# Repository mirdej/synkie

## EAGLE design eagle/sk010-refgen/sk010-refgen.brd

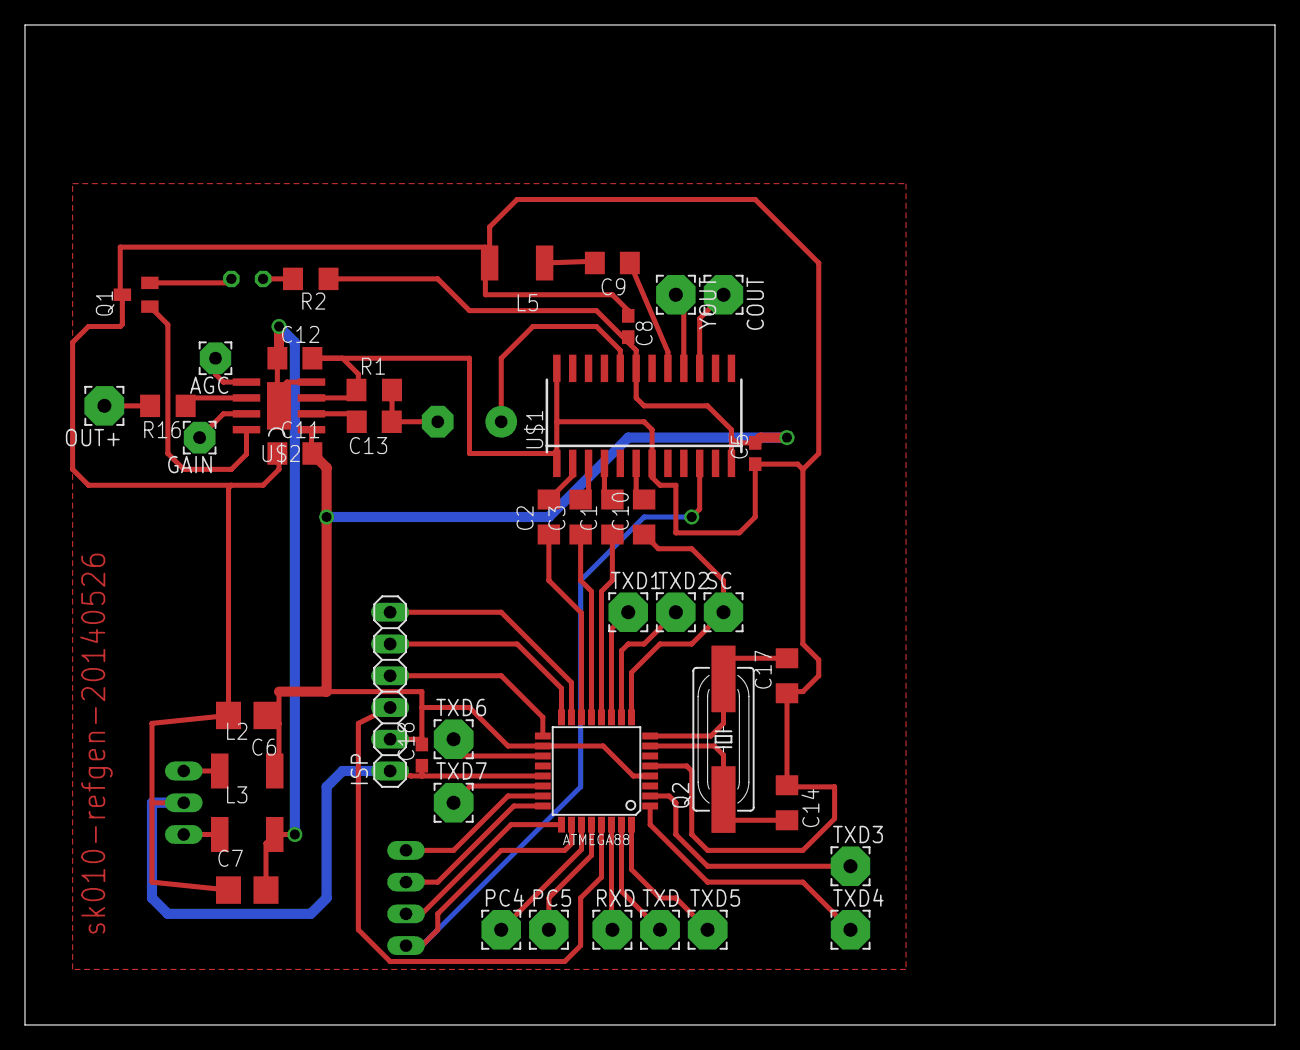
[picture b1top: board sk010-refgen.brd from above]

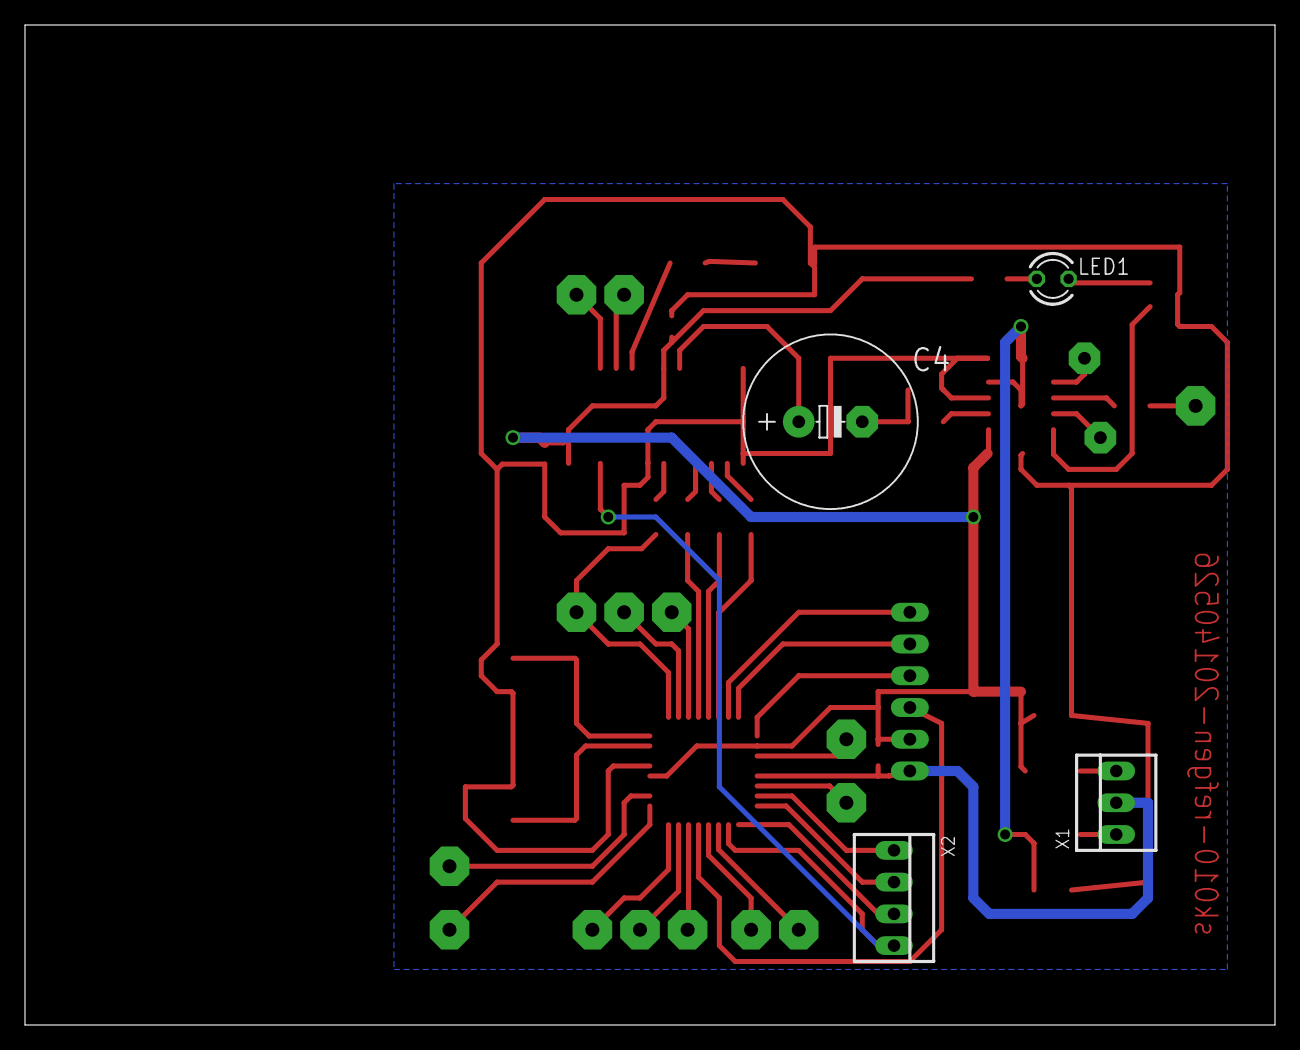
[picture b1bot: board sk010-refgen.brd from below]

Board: 2 copper layers, 100.0 x 80.0 mm, 48 parts (4 on the bottom side), 48 nets.

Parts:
AGC: 2,54/1,0
ATMEGA88: ATMEGA88; TQFP32-08
C1, C2, C3, C9, C10, C11, C12: C1206
C4: E5-13
C5, C8, C18: C0603
C6, C7: 10u; CT3528
C13: 1u; C1206
C14, C17: 15p; C1206
COUT: 3,17/1,1
GAIN: 2,54/1,0
ISP: 1X06
L2, L3, L5: L5038P
LED1: LED3MM
OUT+: 3,17/1,1
PC4, PC5: 3,17/1,1
Q1: BC857ASMD; SOT23-BEC
Q2: 17.734475MHz; HC49UP
R1, R16: 75; R1206
R2: 300; R1206
RXD: 3,17/1,1
SC: 3,17/1,1
TXD, TXD1, TXD2, TXD3, TXD4, TXD5, TXD6, TXD7: 3,17/1,1
U$1: BH7236-RGB; SO24N
U$2: MAX7450; SO08-EXP
X1: 22-23-2031
X2: 22-23-2041
YOUT: 3,17/1,1

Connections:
+5V: ATMEGA88.4, ATMEGA88.18, C5.2, C6.+, C8.2, C11.2, C18.2, ISP.2, L2.2, R2.1, U$1.12, U$1.19, U$2.1
-5V: C7.-, C12.1, L3.2, U$2.4, U$2.EXP
GND: ATMEGA88.5, ATMEGA88.21, C5.1, C6.-, C7.+, C8.1, C11.1, C12.2, C14.1, C17.1, C18.1, ISP.1, L5.2, Q1.C, R1.1, U$1.1, U$1.7, U$1.24, U$2.3, X1.2
MISO: ATMEGA88.16, ISP.5
MOSI: ATMEGA88.15, ISP.6
unnamed: C1.2, U$1.4
unnamed: ATMEGA88.9, C10.1, SC.1
unnamed: C2.2, U$1.2
unnamed: C3.2, U$1.3
unnamed: C9.1, U$1.17
unnamed: C9.2, L5.1
unnamed: ATMEGA88.23, X2.1
unnamed: ATMEGA88.12, C1.1
unnamed: ATMEGA88.25, X2.3
unnamed: ATMEGA88.13, C3.1
unnamed: L2.1, X1.3
unnamed: C10.2, U$1.6
unnamed: AGC.1, U$2.5
unnamed: Q1.B, U$2.8
unnamed: L3.1, X1.1
unnamed: LED1.A, R2.2
unnamed: ATMEGA88.29, ISP.3
unnamed: LED1.K, Q1.E
unnamed: C13.2, U$2.2
unnamed: ATMEGA88.14, C2.1
unnamed: ATMEGA88.26, U$1.10, X2.4
unnamed: GAIN.1, U$2.7
unnamed: C4.-, C13.1, R1.2
unnamed: ATMEGA88.28, PC5.1
unnamed: U$1.16, YOUT.1
unnamed: ATMEGA88.27, PC4.1
unnamed: ATMEGA88.24, X2.2
unnamed: ATMEGA88.22, TXD7.1
unnamed: COUT.1, U$1.15
unnamed: ATMEGA88.30, RXD.1
unnamed: R16.1, U$2.6
unnamed: OUT+.1, R16.2
unnamed: ATMEGA88.7, C14.2, Q2.1
unnamed: ATMEGA88.19, TXD6.1
unnamed: ATMEGA88.31, TXD.1
unnamed: ATMEGA88.32, TXD5.1
unnamed: ATMEGA88.1, TXD4.1
unnamed: ATMEGA88.8, C17.2, Q2.2
unnamed: ATMEGA88.2, TXD3.1
unnamed: ATMEGA88.10, TXD2.1
unnamed: ATMEGA88.11, TXD1.1
unnamed: C4.+, U$1.20
SCK: ATMEGA88.17, ISP.4

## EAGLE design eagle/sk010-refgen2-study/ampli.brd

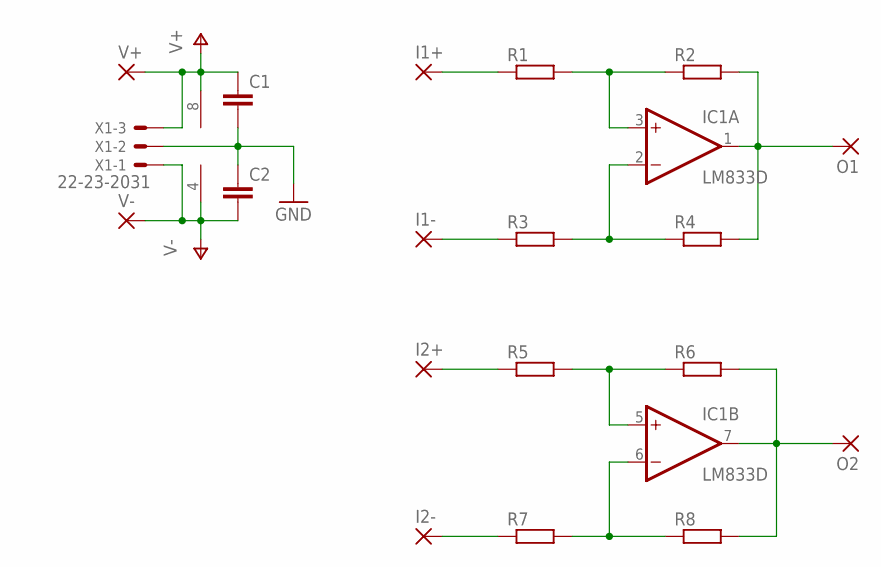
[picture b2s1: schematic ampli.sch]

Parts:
C1, C2: C-EUC0805; C0805
I1+, I1-, I2+, I2-: 3,17/1,1
IC1: LM833D; SO08
O1, O2: 3,17/1,1
R1, R2, R3, R4, R5, R6, R7, R8: R-EU_R1206; R1206
V+: 3,17/1,1
V-: 3,17/1,1
X1: 22-23-2031

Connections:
GND: C1.2, C2.1, X1.2
unnamed: IC1.3 (+IN), R1.2, R2.1
unnamed: IC1.1 (OUT), O1.1, R2.2, R4.2
unnamed: IC1.2 (-IN), R3.2, R4.1
unnamed: I1+.1, R1.1
unnamed: I1-.1, R3.1
unnamed: I2+.1, R5.1
unnamed: IC1.5 (+IN), R5.2, R6.1
unnamed: IC1.7 (OUT), O2.1, R6.2, R8.2
unnamed: IC1.6 (-IN), R7.2, R8.1
unnamed: I2-.1, R7.1
V+: C1.1, IC1.8 (V+), V+.1, X1.3
V-: C2.2, IC1.4 (V-), V-.1, X1.1

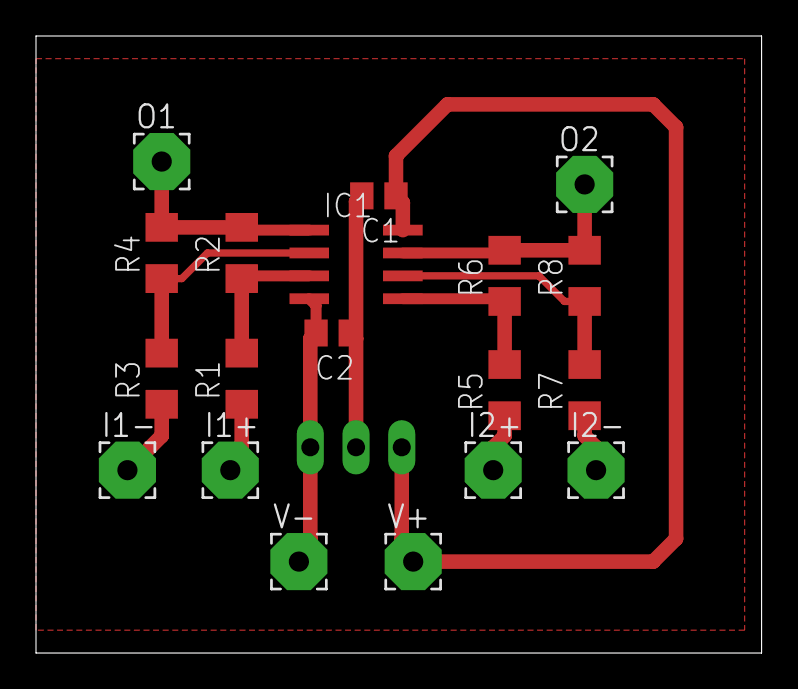
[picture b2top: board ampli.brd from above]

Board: 2 copper layers, 40.3 x 34.3 mm, 20 parts (1 on the bottom side), 13 nets.

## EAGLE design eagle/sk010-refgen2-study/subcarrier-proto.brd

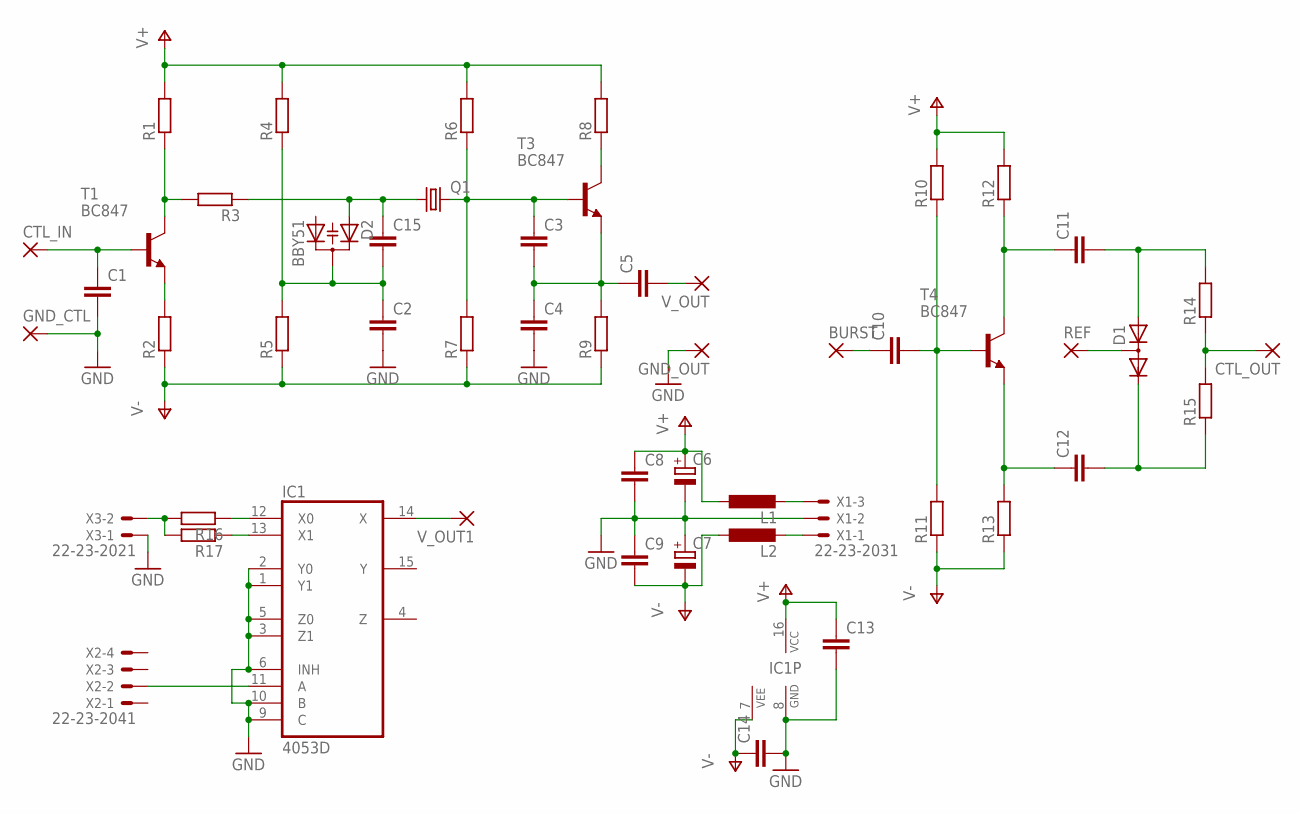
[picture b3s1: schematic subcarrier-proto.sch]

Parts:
BURST: WIREPAD3,17/1,1; 3,17/1,1
C1, C2, C3, C4, C5, C10, C11, C12, C15: C-EUC1210; C1210
C6, C7: CPOL-EUCT3528; CT3528
C8, C9, C13, C14: C-EUC0805; C0805
CTL_IN: WIREPAD3,17/1,1; 3,17/1,1
CTL_OUT: 3,17/1,1
D1: DIODE_2CACA-SOT23; SOT23
D2: BBY51; SOT23
GND_CTL: WIREPAD3,17/1,1; 3,17/1,1
GND_OUT: 3,17/1,1
IC1: 4053D; SO16
L1, L2: L-EUL5038P; L5038P
Q1: CRYSTALHC49UP; HC49UP
R1, R2, R3, R4, R5, R6, R7, R8, R9, R10, R11, R12, R13, R14, R15, R16, R17: R-EU_R1210; R1210
REF: 3,17/1,1
T1, T3, T4: BC847; SOT23
V_OUT, V_OUT1: 3,17/1,1
X1: 22-23-2031
X2: 22-23-2041
X3: 22-23-2021

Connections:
GND: C1.2, C2.2, C4.2, C6.-, C7.+, C8.2, C9.1, C13.2, C14.2, GND_CTL.1, GND_OUT.1, IC1.1 (Y1), IC1.2 (Y0), IC1.3 (Z1), IC1.5 (Z0), IC1.6 (INH), IC1.8 (GND), IC1.9 (C), IC1.10 (B), X1.2, X3.1
unnamed: C1.1, CTL_IN.1, T1.1 (B)
unnamed: C5.2, V_OUT.1
unnamed: R1.1, R3.2, T1.3 (C)
unnamed: R2.2, T1.2 (E)
unnamed: C2.1, C15.2, D2.3 (C), R4.1, R5.2
unnamed: C15.1, D2.1 (A1), Q1.1, R3.1
unnamed: L1.2, X1.3
unnamed: L2.2, X1.1
unnamed: C3.1, Q1.2, R6.1, R7.2, T3.1 (B)
unnamed: R8.1, T3.3 (C)
unnamed: C3.2, C4.1, C5.1, R9.2, T3.2 (E)
unnamed: BURST.1, C10.1
unnamed: C10.2, R10.1, R11.2, T4.1 (B)
unnamed: C12.1, R13.2, T4.2 (E)
unnamed: C11.1, R12.1, T4.3 (C)
unnamed: C11.2, D1.1 (A), R14.2
unnamed: C12.2, D1.2 (C), R15.1
unnamed: CTL_OUT.1, R14.1, R15.2
unnamed: IC1.12 (X0), R16.1
unnamed: IC1.13 (X1), R17.1
unnamed: D1.3 (AC), REF.1
unnamed: R16.2, R17.2, X3.2
unnamed: IC1.11 (A), X2.2
unnamed: IC1.14 (X), V_OUT1.1
V+: C6.+, C8.1, C13.1, IC1.16 (VCC), L1.1, R1.2, R4.2, R6.2, R8.2, R10.2, R12.2
V-: C7.-, C9.2, C14.1, IC1.7 (VEE), L2.1, R2.1, R5.1, R7.1, R9.1, R11.1, R13.1

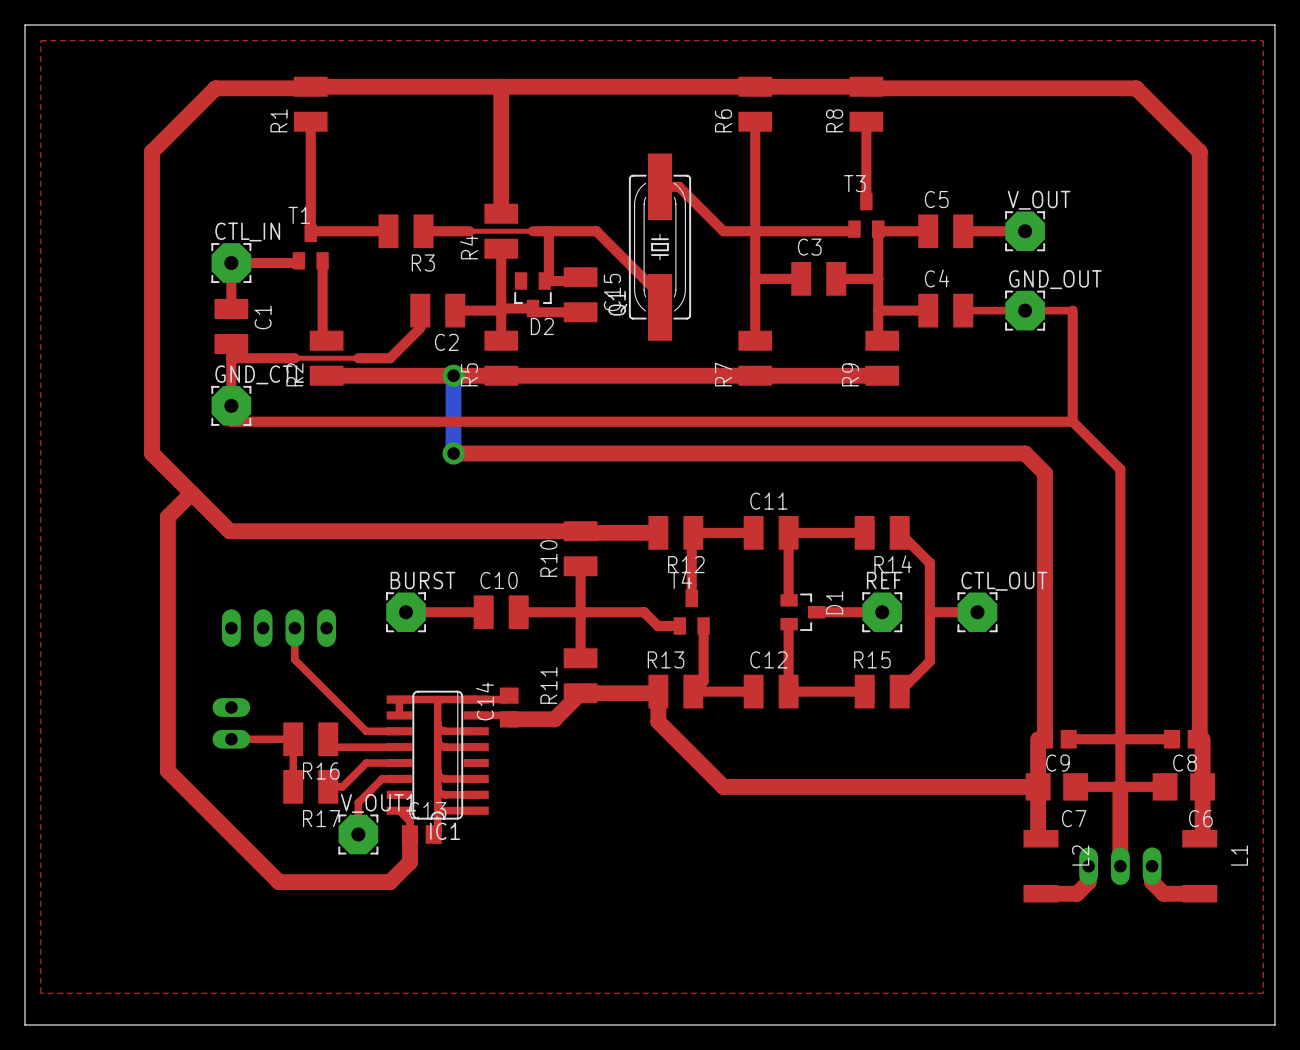
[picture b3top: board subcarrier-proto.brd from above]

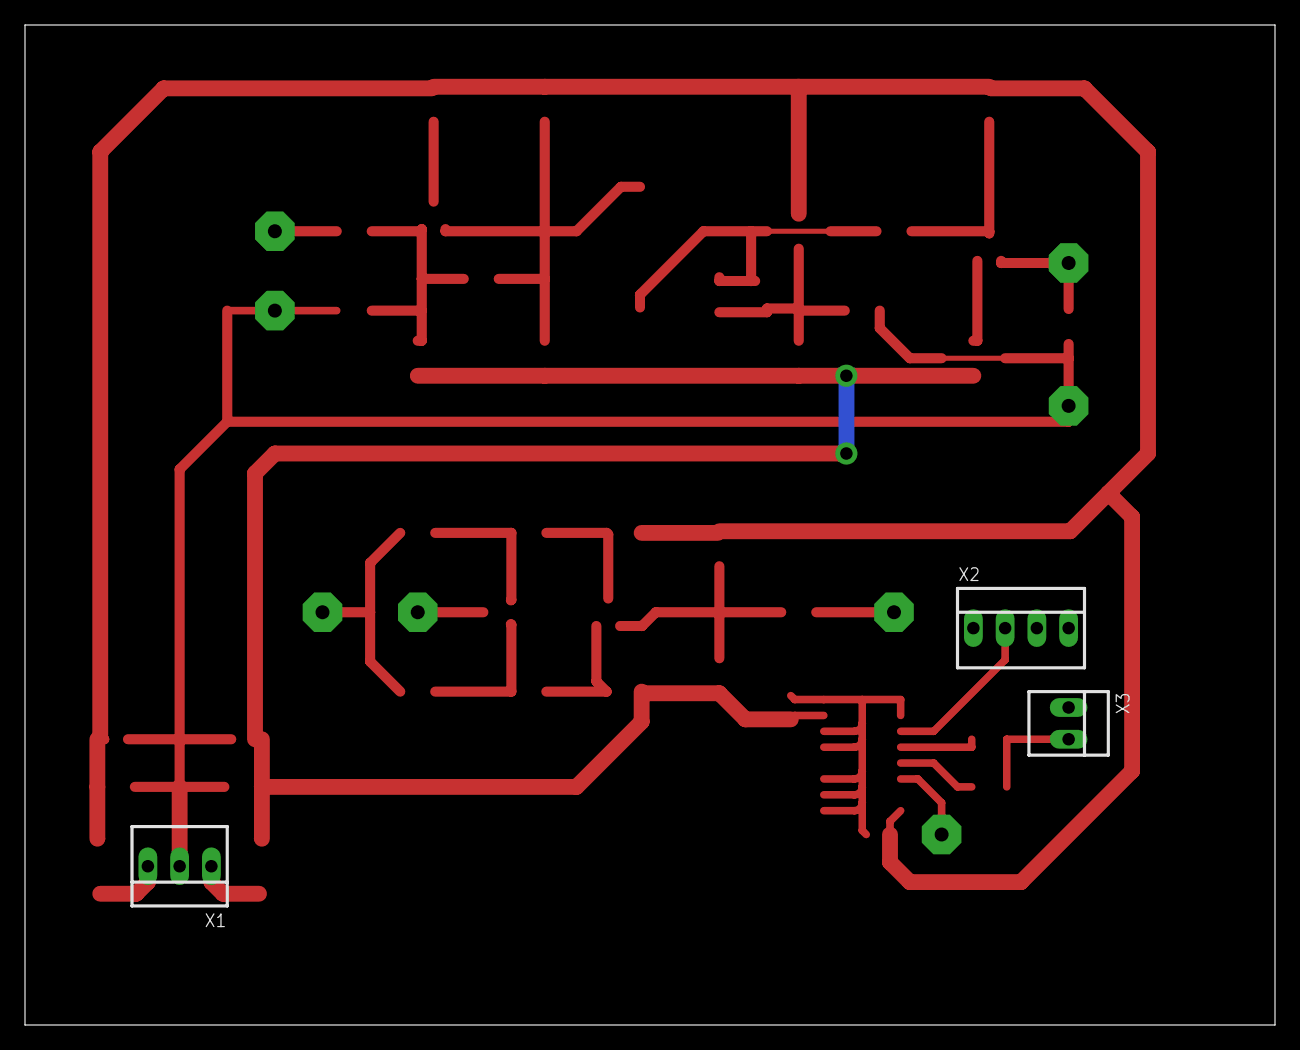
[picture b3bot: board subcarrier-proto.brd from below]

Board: 2 copper layers, 100.0 x 80.0 mm, 52 parts (3 on the bottom side), 27 nets.

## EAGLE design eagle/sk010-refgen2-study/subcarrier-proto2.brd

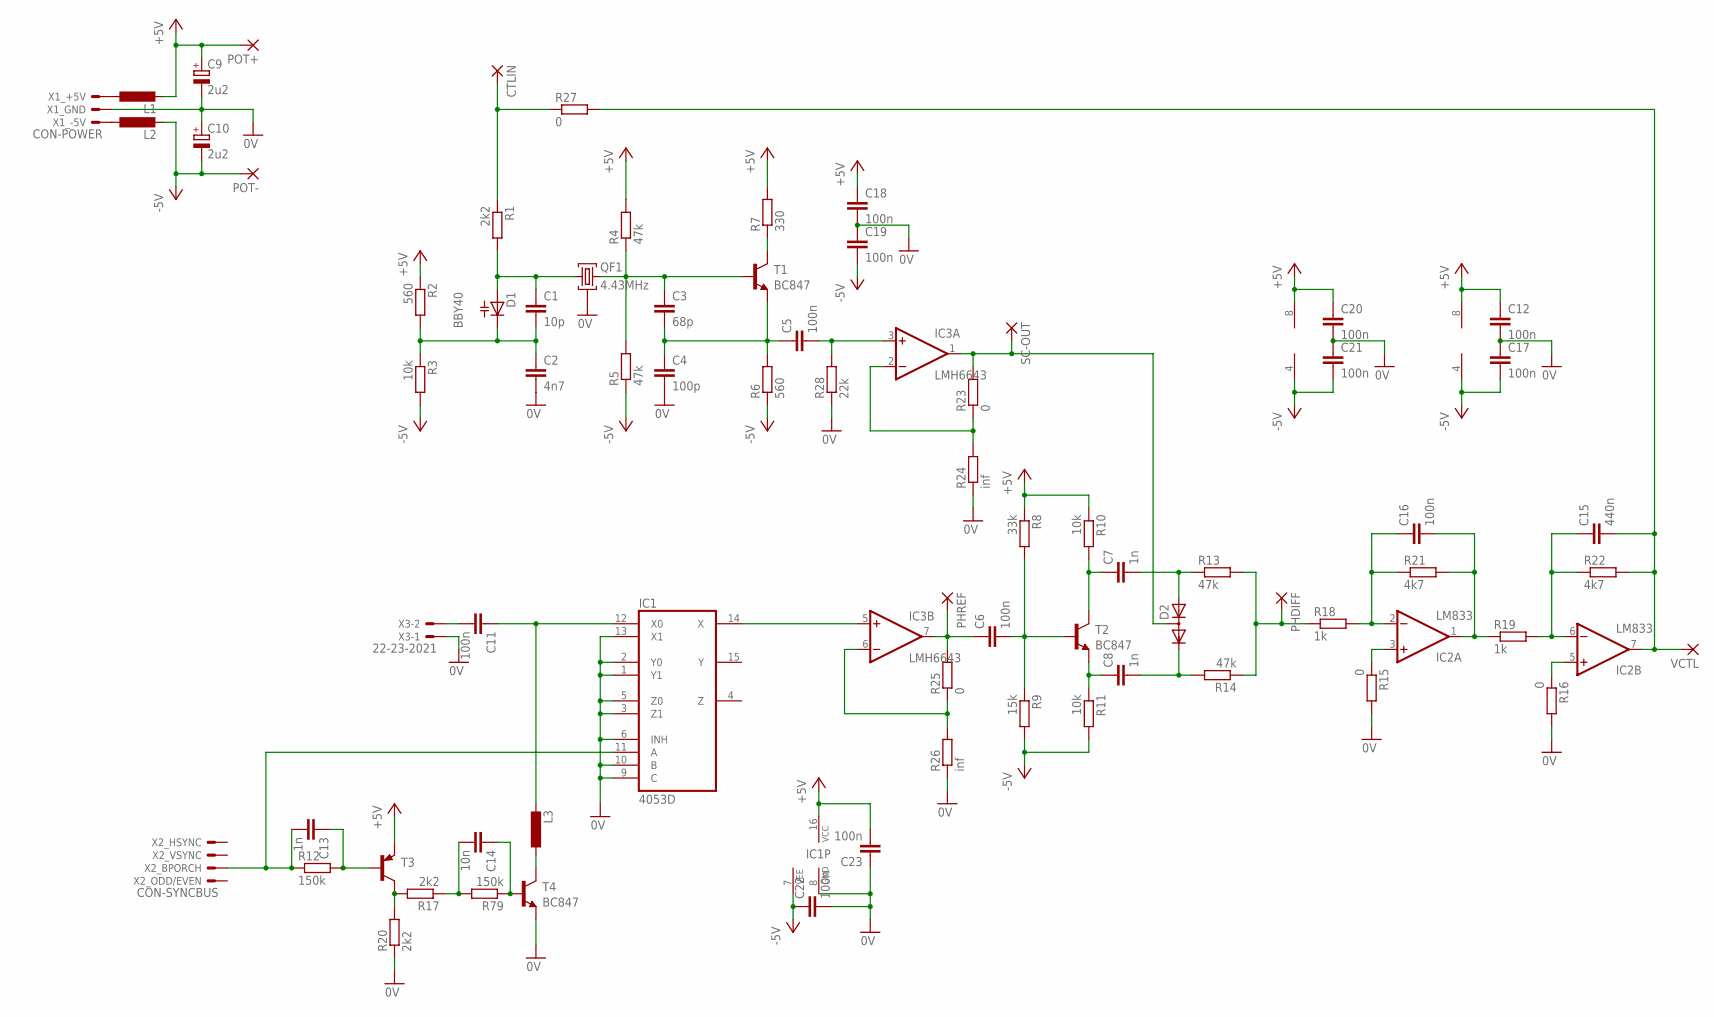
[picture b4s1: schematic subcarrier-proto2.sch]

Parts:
C1: 10p; C1206
C2: 4n7; C1206
C3: 68p; C1206
C4: 100p; C1206
C5, C6, C11, C12, C16, C17, C18, C19, C20, C21, C22, C23: 100n; C1206
C7, C8, C13: 1n; C1206
C9, C10: 2u2; CT3528
C14: 10n; C1206
C15: 440n; C1206
CTLIN: 3,17/1,1
D1: BBY40; SOT23
D2: DIODE_2CACA-SOT23; SOT23
IC1: 4053D; SO16
IC2: LM833; SO08
IC3: LMH6643; SO08
L1, L2, L3: L-EUL5038P; L5038P
PHDIFF: 3,17/1,1
PHREF: 3,17/1,1
POT+: 3,17/1,1
POT-: 3,17/1,1
QF1: 4.43MHz; SMD-CRYSTAL-GND
R1, R17, R20: 2k2; R1206
R2, R6: 560; R1206
R3, R10, R11: 10k; R1206
R4, R5, R13, R14: 47k; R1206
R7: 330; R1206
R8: 33k; R1206
R9: 15k; R1206
R12, R79: 150k; R1206
R15, R16, R23, R25, R27: 0; R1206
R18, R19: 1k; R1206
R21, R22: 4k7; R1206
R24, R26: inf; R1206
R28: 22k; R1206
SC-OUT: 3,17/1,1
T1, T2, T4: BC847; SOT23-BEC
T3: TRANS-PNPSOT23-BEC; SOT23-BEC
VCTL: 3,17/1,1
X1: CON-POWER; 22-23-2031
X2: CON-SYNCBUS; 22-23-2041
X3: 22-23-2021

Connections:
0V: C2.2, C4.2, C9.-, C10.+, C12.2, C17.1, C18.2, C19.1, C20.2, C21.1, C22.2, C23.1, IC1.1 (Y1), IC1.2 (Y0), IC1.3 (Z1), IC1.5 (Z0), IC1.6 (INH), IC1.8 (GND), IC1.9 (C), IC1.10 (B), IC1.13 (X1), QF1.P$3 (2), R15.2, R16.2, R20.1, R24.1, R26.1, R28.1, T4.E, X1.2, X3.1
+5V: C9.+, C12.1, C18.1, C20.1, C23.2, IC1.16 (VCC), IC2.8 (V+), IC3.8 (V+), L1.2, POT+.1, R2.1, R4.2, R7.2, R8.1, R10.1, T3.E
-5V: C10.-, C17.2, C19.2, C21.2, C22.1, IC1.7 (VEE), IC2.4 (V-), IC3.4 (V-), L2.2, POT-.1, R3.2, R5.1, R6.1, R9.2, R11.2
unnamed: C13.1, R12.2, T3.B
unnamed: C13.2, IC1.11 (A), R12.1, X2.2
unnamed: C1.1, D1.1 (A1), QF1.P$1 (1), R1.2
unnamed: C3.1, QF1.P$2 (3), R4.1, R5.2, T1.B
unnamed: C1.2, C2.1, D1.3 (C), R2.2, R3.1
unnamed: C3.2, C4.1, C5.1, R6.2, T1.E
unnamed: C5.2, IC3.3 (+IN), R28.2
unnamed: R7.1, T1.C
unnamed: C6.2, R8.2, R9.1, T2.B
unnamed: C8.1, R11.1, T2.E
unnamed: C7.1, R10.2, T2.C
unnamed: PHDIFF.1, R13.2, R14.1, R18.1
unnamed: C7.2, D2.1 (A), R13.1
unnamed: C8.2, D2.2 (C), R14.2
unnamed: C6.1, IC3.7 (OUT), PHREF.1, R25.2
unnamed: C11.2, X3.2
unnamed: C11.1, IC1.12 (X0), L3.2
unnamed: C16.1, IC2.2 (-IN), R18.2, R21.1
unnamed: IC2.3 (+IN), R15.1
unnamed: IC2.5 (+IN), R16.1
unnamed: C16.2, IC2.1 (OUT), R19.1, R21.2
unnamed: C15.1, IC2.6 (-IN), R19.2, R22.1
unnamed: C15.2, IC2.7 (OUT), R22.2, R27.2, VCTL.1
unnamed: L1.1, X1.3
unnamed: L2.1, X1.1
unnamed: CTLIN.1, R1.1, R27.1
unnamed: D2.3 (AC), IC3.1 (OUT), R23.2, SC-OUT.1
unnamed: IC3.2 (-IN), R23.1, R24.2
unnamed: IC3.6 (-IN), R25.1, R26.2
unnamed: IC1.14 (X), IC3.5 (+IN)
unnamed: L3.1, T4.C
unnamed: C14.1, R79.1, T4.B
unnamed: R17.2, R20.2, T3.C
unnamed: C14.2, R17.1, R79.2

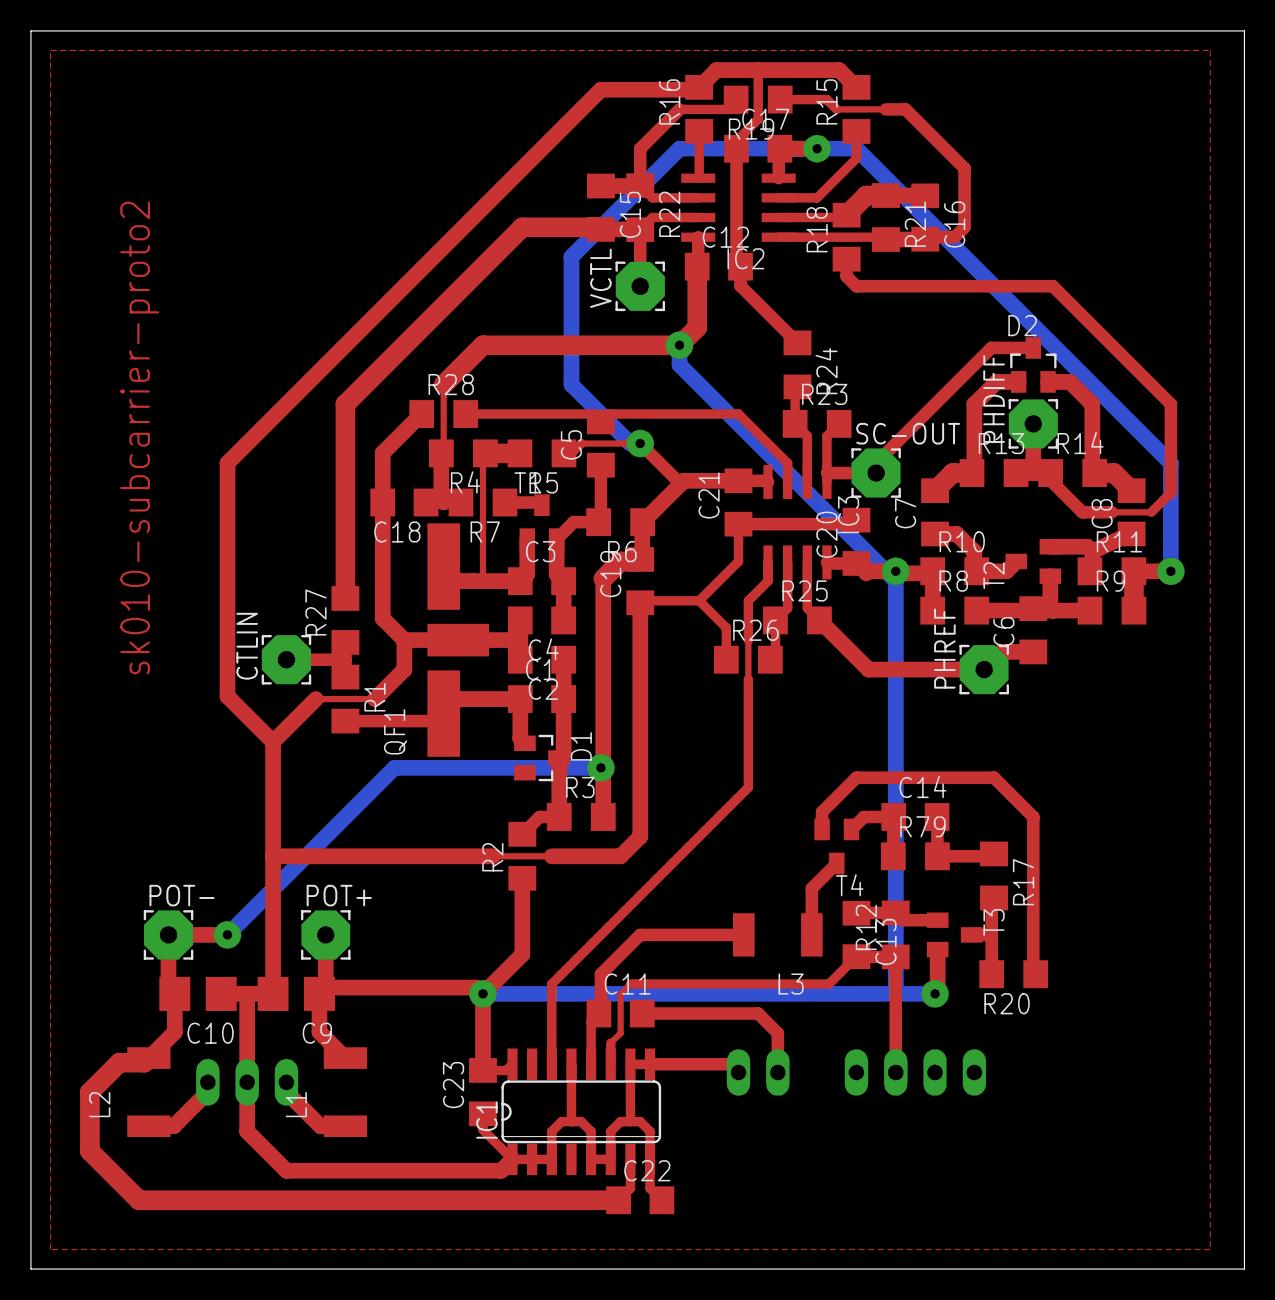
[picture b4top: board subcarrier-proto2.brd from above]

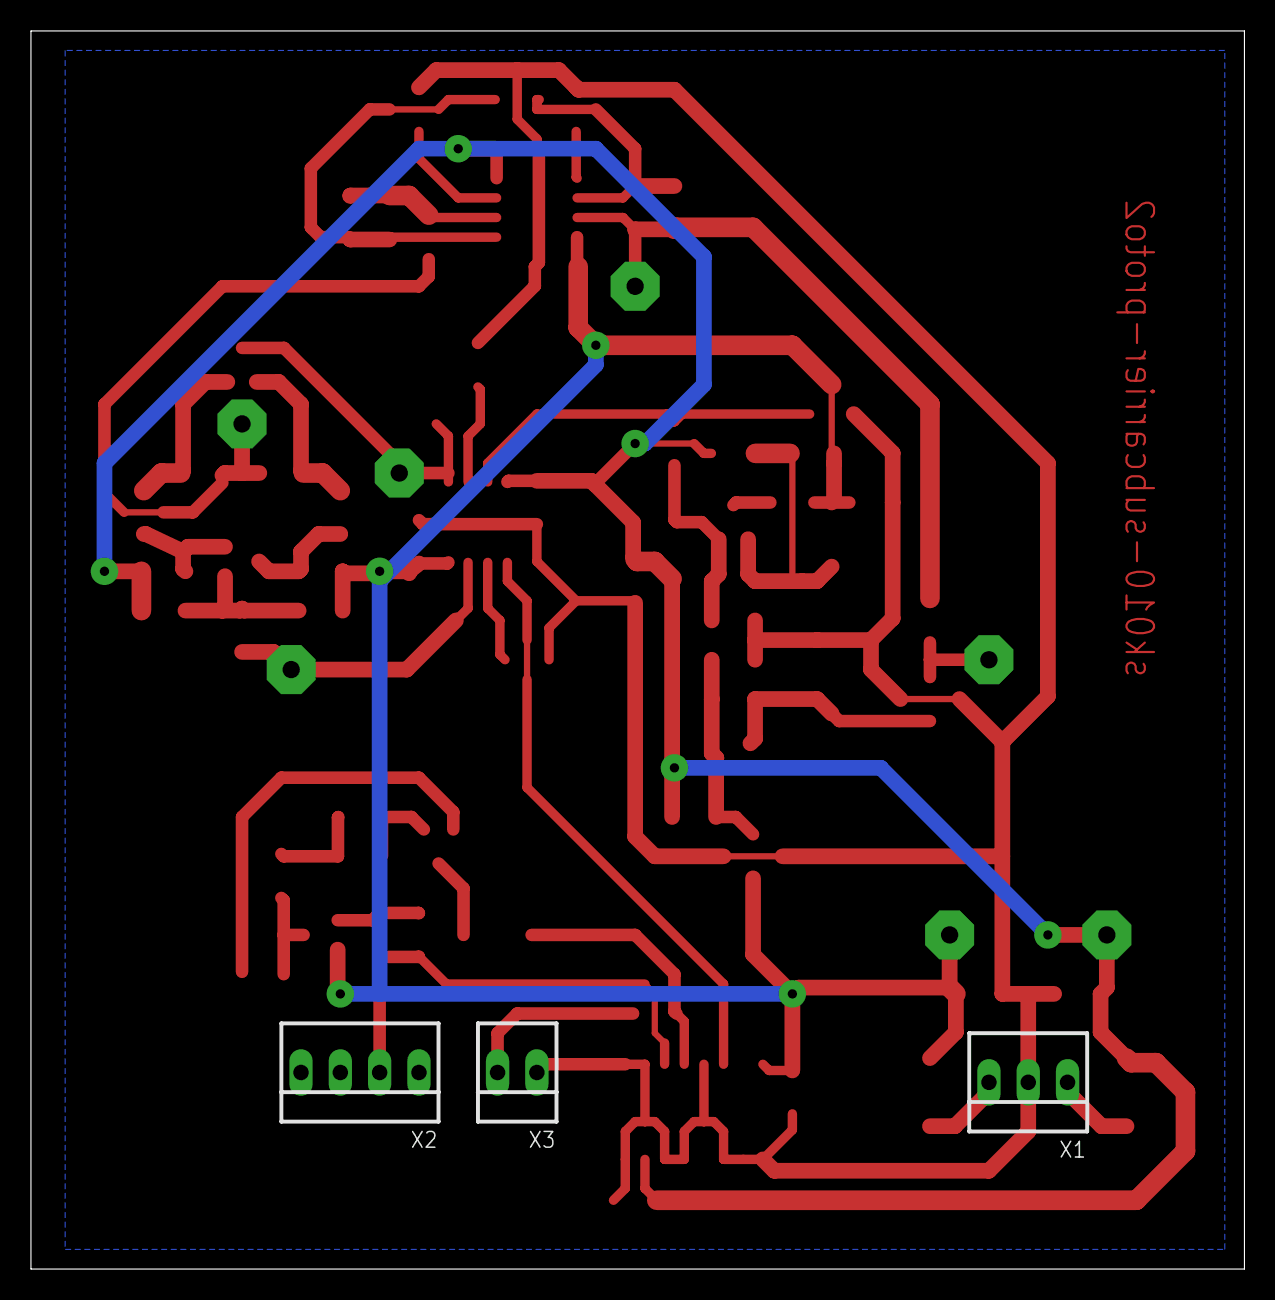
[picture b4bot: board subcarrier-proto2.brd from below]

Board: 2 copper layers, 78.4 x 80.0 mm, 75 parts (3 on the bottom side), 37 nets.

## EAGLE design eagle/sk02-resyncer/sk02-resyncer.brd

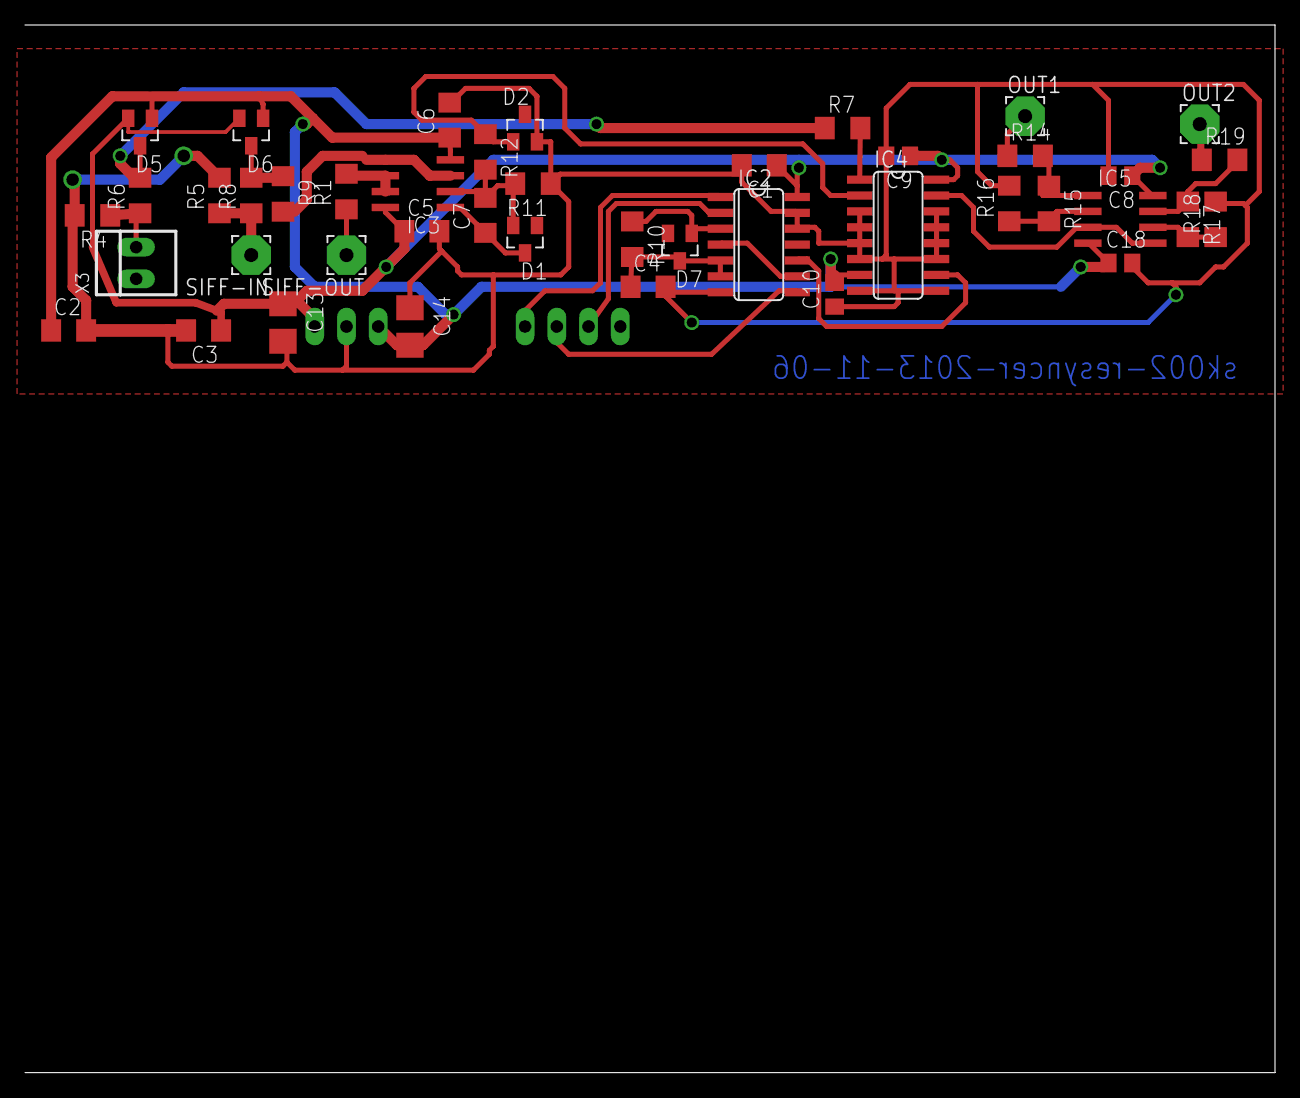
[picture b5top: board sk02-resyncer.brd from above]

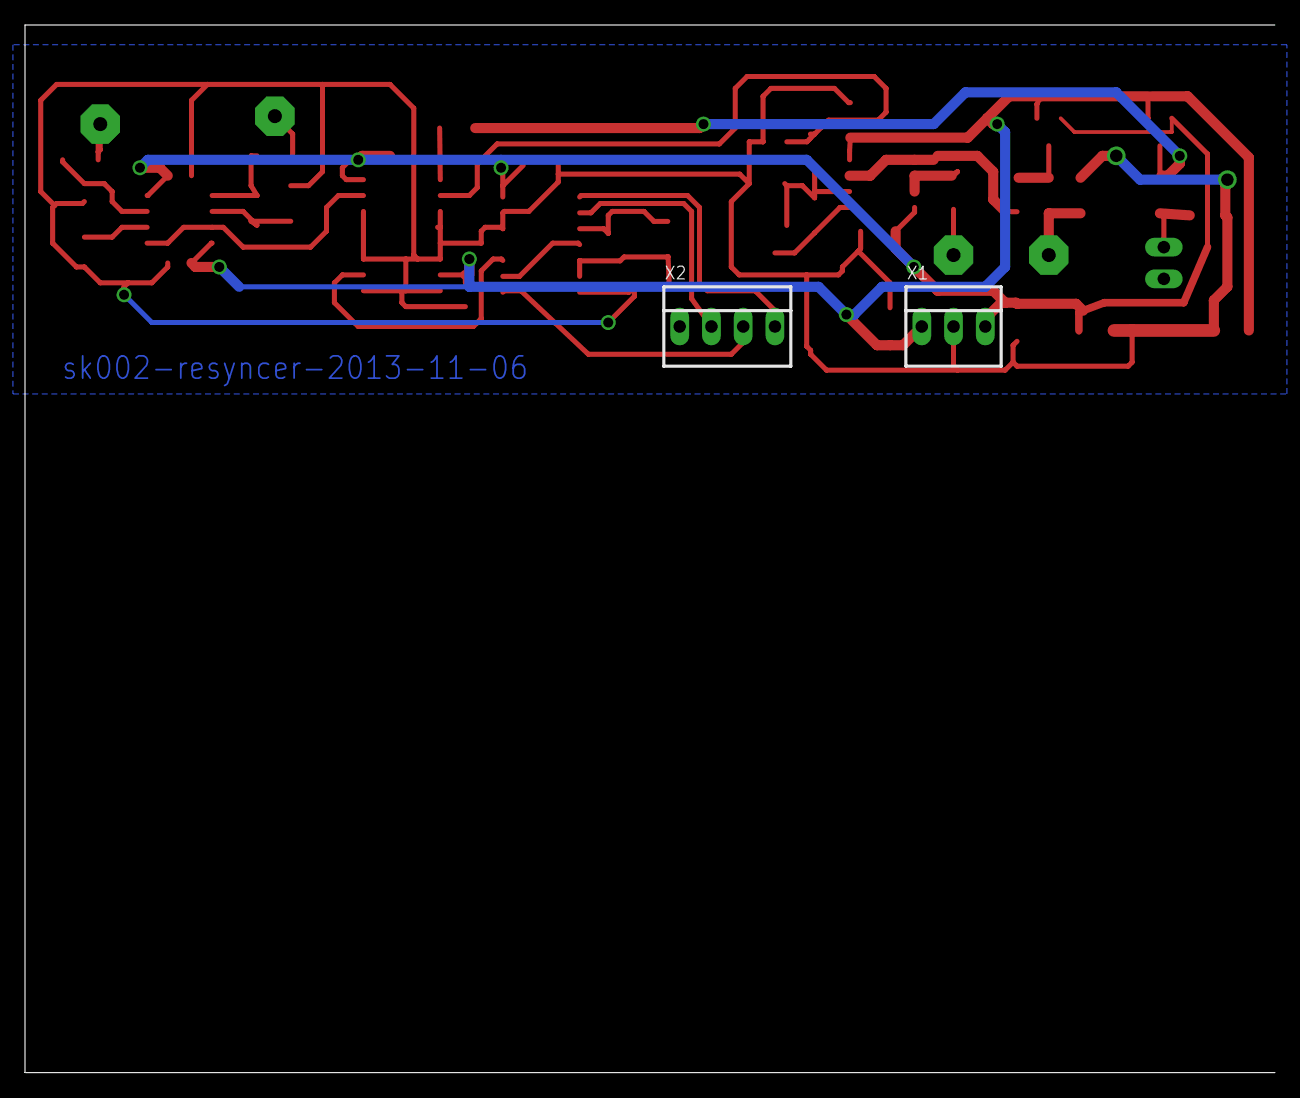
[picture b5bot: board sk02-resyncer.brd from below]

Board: 2 copper layers, 100.0 x 83.8 mm, 45 parts (2 on the bottom side), 28 nets.

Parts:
C1, C2, C3, C5, C6: 100n; C1206
C4: 120p; C1206
C7: 10p; C1206
C8, C9, C10, C18: 100n; C0805
C13, C14: 2u2tantal; CT3528
D1, D5, D6: BAT54S-L44; SOT23
D2: 1PS302; SOT23
D7: BAS70-04; SOT23
IC2: 4011D; SO14
IC3, IC5: LM833D; SO08
IC4: 4053D; SO16
OUT1, OUT2: 3,17/1,1
R1, R14, R19: 75; R1206
R4, R5: 47k; R1206
R6, R7, R8, R9: 100; R1206
R10: 2k2; R1206
R11, R12: 1k; R1206
R15, R16, R17, R18: 200; R1206
SIFF-IN: 3,17/1,1
SIFF-OUT: 3,17/1,1
X1: 22-23-2031
X2: 22-23-2041
X3: 22-23-2021

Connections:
+5V: C1.1, C3.1, C5.1, C8.1, C9.1, C13.+, D5.2, D6.2, IC2.14, IC3.8, IC4.16, IC5.8, X1.3
-5V: C2.1, C6.1, C10.2, C14.-, C18.1, D5.1, D6.1, IC3.4, IC4.7, IC5.4, X1.1
AGND: C1.2, C2.2, C3.2, C4.2, C5.2, C6.2, C8.2, C9.2, C10.1, C13.-, C14.+, C18.2, D2.2, IC2.7, IC2.12, IC2.13, IC4.3, IC4.4, IC4.5, IC4.6, IC4.8, IC4.9, IC4.11, IC4.12, IC4.13, IC4.14, R4.2, R5.2, R11.1, R16.2, R18.2, X1.2
BACKPORCH: IC2.2, X2.2
H-SYNC: IC2.1, X2.4
unnamed: IC3.6, IC3.7, R1.2
unnamed: R4.1, R6.1, X3.2
unnamed: D5.3, R6.2, R7.1
unnamed: C4.1, D7.3, IC2.5, IC2.6, R10.2
unnamed: IC4.1, R7.2
unnamed: D2.1, IC4.2, R12.1
unnamed: IC2.4, IC2.9
unnamed: D7.1, IC2.3, R10.1
unnamed: R1.1, SIFF-OUT.1
unnamed: IC3.3, IC3.5, R9.2
unnamed: IC2.10, IC4.10
unnamed: C7.1, D1.3, IC3.1
unnamed: R5.1, R8.1, SIFF-IN.1
unnamed: D6.3, R8.2, R9.1
unnamed: C7.2, D1.2, IC3.2, R11.2, R12.2
unnamed: IC5.2, R15.2, R16.1
unnamed: IC5.1, R14.2, R15.1
unnamed: IC4.15, IC5.3, IC5.5
unnamed: IC5.6, R17.2, R18.1
unnamed: IC5.7, R17.1, R19.2
unnamed: OUT1.1, R14.1
unnamed: OUT2.1, R19.1
V-SYNC: IC2.8, X2.3

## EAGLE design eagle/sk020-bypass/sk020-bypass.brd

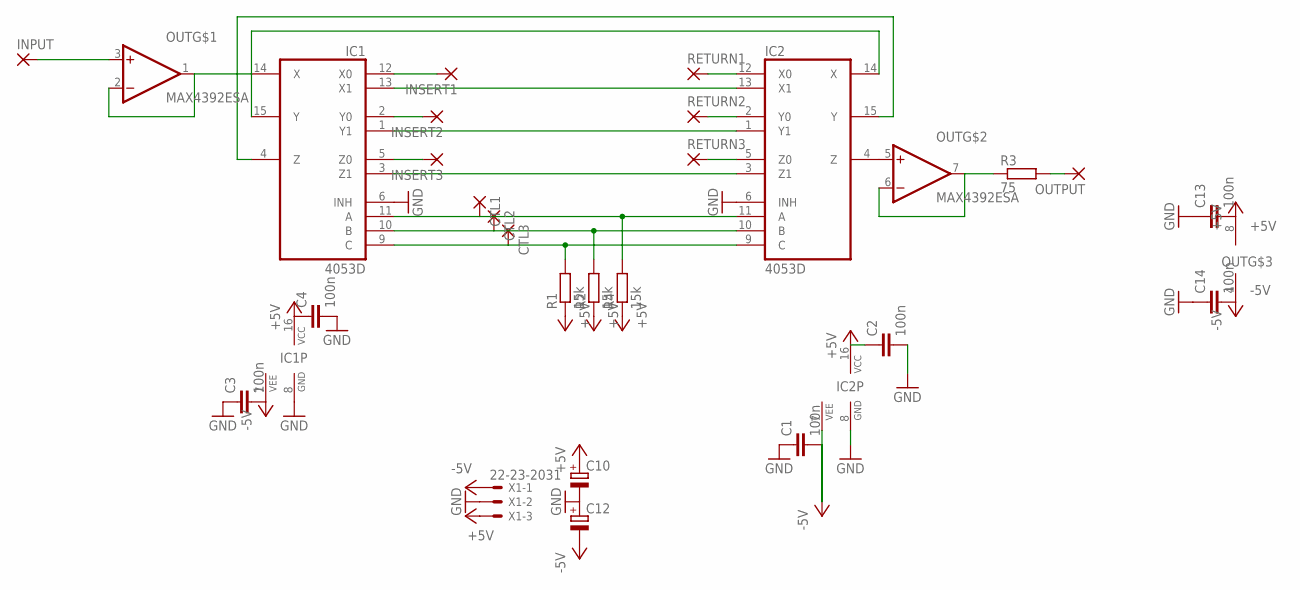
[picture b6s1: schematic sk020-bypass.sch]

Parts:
C1, C2, C3, C4, C13, C14: 100n; C0805
C10, C12: CPOL-EUSMCB; SMC_B
CTL1, CTL2, CTL3: 3,17/1,1
IC1, IC2: 4053D; SO16
INPUT: 3,17/1,1
INSERT1, INSERT2, INSERT3: 3,17/1,1
OUT: MAX4392ESA; SO08
OUTPUT: 3,17/1,1
R1, R2, R4: 15k; R1206
R3: 75; R1206
RETURN1, RETURN2, RETURN3: 3,17/1,1
X1: 22-23-2031

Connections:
+5V: C2.1, C4.1, C10.+, C13.2, IC1.16 (VCC), IC2.16 (VCC), OUT.8 (+5V), R1.1, R2.1, R4.1, X1.3
-5V: C1.2, C3.2, C12.-, C14.2, IC1.7 (VEE), IC2.7 (VEE), OUT.4 (-5V), X1.1
GND: C1.1, C2.2, C3.1, C4.2, C10.-, C12.+, C13.1, C14.1, IC1.6 (INH), IC1.8 (GND), IC2.6 (INH), IC2.8 (GND), X1.2
unnamed: IC1.12 (X0), INSERT1.1
unnamed: INPUT.1, OUT.3 (+IN)
unnamed: IC1.15 (Y), IC2.14 (X)
unnamed: IC1.2 (Y0), INSERT2.1
unnamed: IC1.5 (Z0), INSERT3.1
unnamed: IC1.4 (Z), IC2.15 (Y)
unnamed: IC2.12 (X0), RETURN1.1
unnamed: IC1.14 (X), OUT.1 (OUT), OUT.2 (-IN)
unnamed: OUTPUT.1, R3.2
unnamed: IC2.4 (Z), OUT.5 (+IN)
unnamed: IC2.2 (Y0), RETURN2.1
unnamed: IC2.5 (Z0), RETURN3.1
unnamed: IC1.13 (X1), IC2.13 (X1)
unnamed: IC1.1 (Y1), IC2.1 (Y1)
unnamed: IC1.3 (Z1), IC2.3 (Z1)
unnamed: CTL1.1, IC1.11 (A), IC2.11 (A), R4.2
unnamed: CTL2.1, IC1.10 (B), IC2.10 (B), R2.2
unnamed: CTL3.1, IC1.9 (C), IC2.9 (C), R1.2
unnamed: OUT.6 (-IN), OUT.7 (OUT), R3.1
